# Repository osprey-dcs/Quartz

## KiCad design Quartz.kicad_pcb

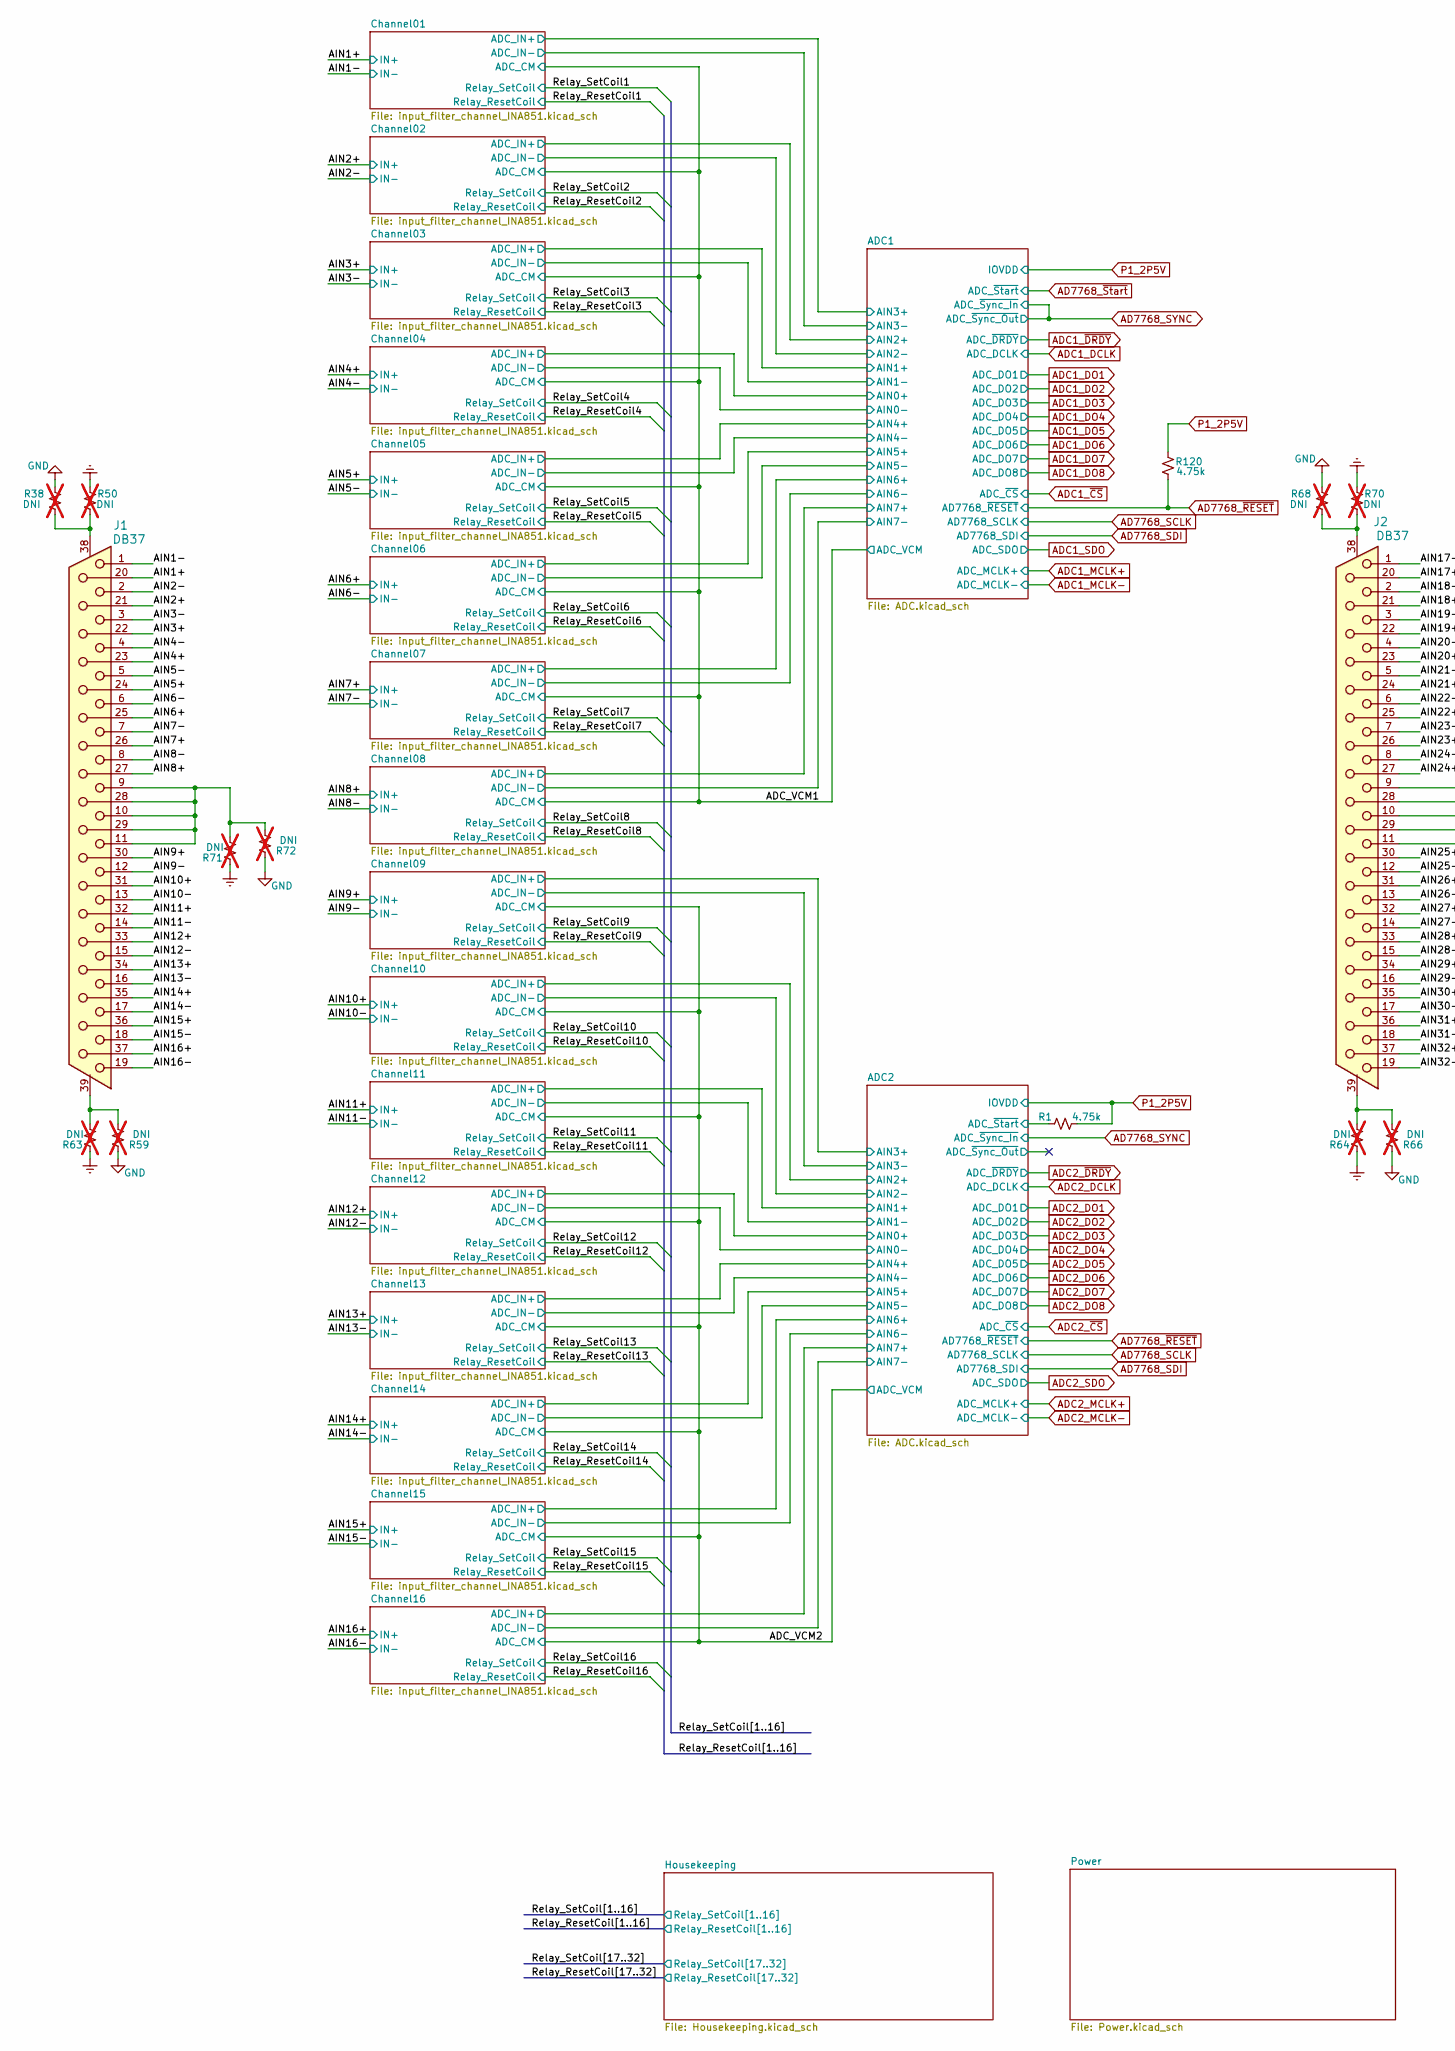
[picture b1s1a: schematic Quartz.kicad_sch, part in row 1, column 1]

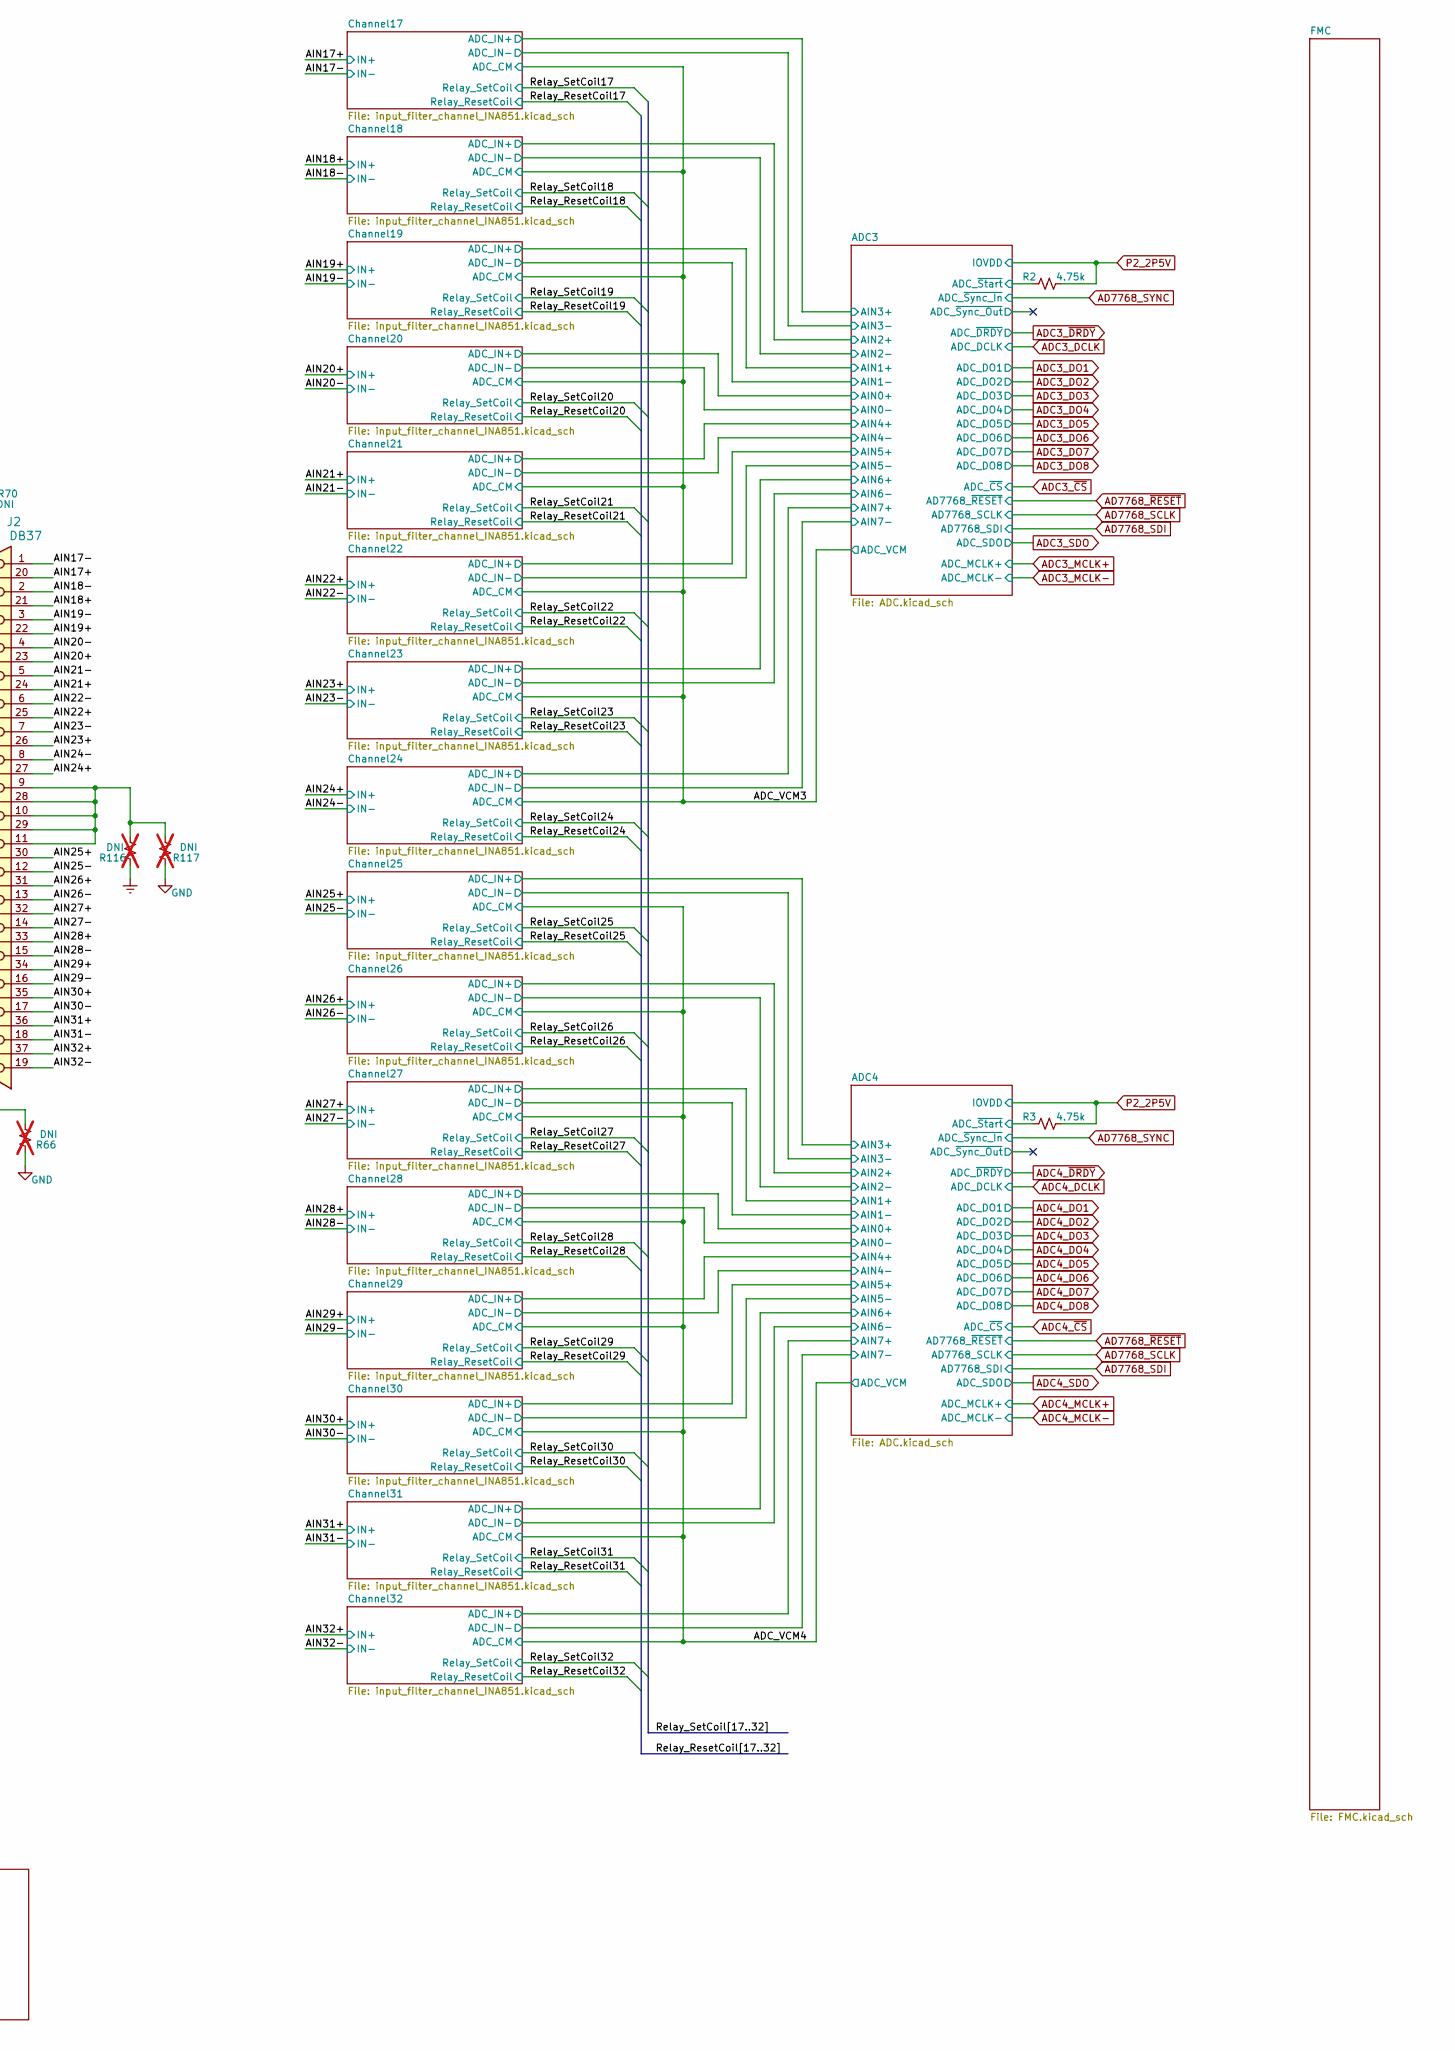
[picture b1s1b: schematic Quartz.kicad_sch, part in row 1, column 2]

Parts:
J1, J2: DB37; CONN_5747847-6_TYC; MPN 5747847-6
R1, R2, R3, R120: 4.75k; R_0402_1005Metric; MPN RC0402FR-074K75L
R38, R50, R59, R63, R64, R66, R68, R70, R71, R72, R116, R117: DNI; R_0805_2012Metric; MPN DNI; not fitted

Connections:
/ADC2/ADC_~Start: R1.1; also elsewhere on the board
/ADC3/ADC_~Start: R2.1; also elsewhere on the board
/ADC4/ADC_~Start: R3.1; also elsewhere on the board
/AIN1+: J1.20; also elsewhere on the board
/AIN1-: J1.1; also elsewhere on the board
/AIN2+: J1.21; also elsewhere on the board
/AIN2-: J1.2; also elsewhere on the board
/AIN3+: J1.22; also elsewhere on the board
/AIN3-: J1.3; also elsewhere on the board
/AIN4+: J1.23; also elsewhere on the board
/AIN4-: J1.4; also elsewhere on the board
/AIN5+: J1.24; also elsewhere on the board
/AIN5-: J1.5; also elsewhere on the board
/AIN6+: J1.25; also elsewhere on the board
/AIN6-: J1.6; also elsewhere on the board
/AIN7+: J1.26; also elsewhere on the board
/AIN7-: J1.7; also elsewhere on the board
/AIN8+: J1.27; also elsewhere on the board
/AIN8-: J1.8; also elsewhere on the board
/AIN9+: J1.30; also elsewhere on the board
/AIN9-: J1.12; also elsewhere on the board
/AIN10+: J1.31; also elsewhere on the board
/AIN10-: J1.13; also elsewhere on the board
/AIN11+: J1.32; also elsewhere on the board
/AIN11-: J1.14; also elsewhere on the board
/AIN12+: J1.33; also elsewhere on the board
/AIN12-: J1.15; also elsewhere on the board
/AIN13+: J1.34; also elsewhere on the board
/AIN13-: J1.16; also elsewhere on the board
/AIN14+: J1.35; also elsewhere on the board
/AIN14-: J1.17; also elsewhere on the board
/AIN15+: J1.36; also elsewhere on the board
/AIN15-: J1.18; also elsewhere on the board
/AIN16+: J1.37; also elsewhere on the board
/AIN16-: J1.19; also elsewhere on the board
/AIN17+: J2.20; also elsewhere on the board
/AIN17-: J2.1; also elsewhere on the board
/AIN18+: J2.21; also elsewhere on the board
/AIN18-: J2.2; also elsewhere on the board
/AIN19+: J2.22; also elsewhere on the board
/AIN19-: J2.3; also elsewhere on the board
/AIN20+: J2.23; also elsewhere on the board
/AIN20-: J2.4; also elsewhere on the board
/AIN21+: J2.24; also elsewhere on the board
/AIN21-: J2.5; also elsewhere on the board
/AIN22+: J2.25; also elsewhere on the board
/AIN22-: J2.6; also elsewhere on the board
/AIN23+: J2.26; also elsewhere on the board
/AIN23-: J2.7; also elsewhere on the board
/AIN24+: J2.27; also elsewhere on the board
/AIN24-: J2.8; also elsewhere on the board
/AIN25+: J2.30; also elsewhere on the board
/AIN25-: J2.12; also elsewhere on the board
/AIN26+: J2.31; also elsewhere on the board
/AIN26-: J2.13; also elsewhere on the board
/AIN27+: J2.32; also elsewhere on the board
/AIN27-: J2.14; also elsewhere on the board
/AIN28+: J2.33; also elsewhere on the board
/AIN28-: J2.15; also elsewhere on the board
/AIN29+: J2.34; also elsewhere on the board
/AIN29-: J2.16; also elsewhere on the board
/AIN30+: J2.35; also elsewhere on the board
/AIN30-: J2.17; also elsewhere on the board
/AIN31+: J2.36; also elsewhere on the board
/AIN31-: J2.18; also elsewhere on the board
/AIN32+: J2.37; also elsewhere on the board
/AIN32-: J2.19; also elsewhere on the board
AD7768_~RESET: R120.1; also elsewhere on the board
Earth: R50.1, R63.1, R64.1, R70.1, R71.1, R116.1; also elsewhere on the board
GND: R38.1, R59.1, R66.1, R68.1, R72.1, R117.1; also elsewhere on the board
unnamed: J1.9, J1.10, J1.11, J1.28, J1.29, R71.2, R72.2
unnamed: J1.38, R38.2, R50.2
unnamed: J1.39, R59.2, R63.2
unnamed: J2.9, J2.10, J2.11, J2.28, J2.29, R116.2, R117.2
unnamed: J2.38, R68.2, R70.2
unnamed: J2.39, R64.2, R66.2
P1_2P5V: R1.2, R120.2; also elsewhere on the board
P2_2P5V: R2.2, R3.2; also elsewhere on the board

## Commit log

2023-12-28 Inital Commit
    Inital Commit
2024-01-02 Updated Schmatics
    Some outdated schematics were in the init commit. Uploded proper revision with tweaks.
2024-01-03 Fixed FMC mapping Issue
    Fixed FMC pin mapping and added FMC pin mapping excel file
2024-01-04 Updated Schematics with recent changes
    Made Updates with recent suggestions.
2024-01-04 Updated Channel 1 and fixes from review
    Updated Channel 1 to use the INA851.
    Fixed the ORNTA part pinout.
    Fixed feedback on LT1763s.
2024-01-08 Schmatic Updates
    Updated:
    ADC MCLK signal
    Removed PMOD connectors
    Added Coax input for iRIG signal with 5V buffer
    Moved around FMC pin mapping
    Changed relay driver chip daisy chain order
2024-01-09 Updated Schematics
    Changes:
    -Moved Input resistors to after Coupling Relay
    -Added diff cap at ADC input
    -Changed the ADC clocking configuration (added quad LVDS driver)
    -Changed some signal names for consistancy
2024-01-11 Updated Schematics with latest suggestions
    updates:
    -Revised Power supply section
    -Changed clock buffer chip for ADC Clock
    - Added additional no pop & jumper parts for board debugging
    -Other small part changes
2024-01-12 Schematic Updates
    Updated:
    -Fixed AMC7823 labels
    -Added present detect signals on FMC
    -Added ferrite beads in Power Section and AFE
    -Added 0R in power section
    -Revised EEPROM connections
2024-01-16 Updated Schematic
    -Changed PPS input signal buffer
    -Made Tweaks to Power Supply section (Many involving the LT3097) as suggested by Trent.
    - general schematic clean up for readability
2024-01-18 Update to Schematics; initial PCB commit
    -Updated Power, Housekeeping, and ADCs sheets.
    -Remapped FMC pins
    -Initial board layout commit
2024-01-22 Updated Layout
    -Additional Layout Work
2024-01-23 Updated Schematics with all suggestions
    -Added pull up resistors on SDO line to FPGA
    -Fixed some I/O flags to properly indicate direction
    -Added Bulk caps on 15V rails
    -Added series caps to AC couple the LVDS clock lines. See AN408 from the manufacture
    -Add Voltage monitor for 1.8V and 5V
2024-01-24 Updated Project
    Schematics:
    -updated level shifting IC's
    -Add notes to level shifters
    -Changed Relay Coil Driver channel mapping
    -Added additional Mounting Hole
    Layout
2024-01-25 Updated Project with Latest Changes
    Project:
    -Added pdf plots of PCB layout
    Schematics:
    -Fixed L8 Pinout
    -Adjusted FMC connections
    -Adjusted level shifter connections
2024-01-26 Push Version before ADC change from 1.8V to 2.5V I/O
2024-01-26 Changed ADCs to run on +2.5V VADJ
    Modified schematic to allow the ADCs to be run from the +2.5V VADJ inputs on the FMC connector.
    -All relevant ERC issues ran been looked into.
    -Still working on all Board DRC issues.
2024-01-29 Completed Schmatic and Layout
    All Schematic and Layout Task are complete with the following exceptions:
    - Adjust Silkscreen Layers
    - Add Osprey Logo and Serial Number
    Note-Removed Files no longer reference in the project
2024-01-29 Updated PCB
    Adjusted Silkscreen
    Added Logo and SN location
2024-01-31 Finalized Design & Board
    Change to design
    -Added resistor options to choose the grounding of input connectors
    -uploaded libraries
    -uploaded generated BOM
    - adjusted mounting holes on front of board by 10mil
    -Changed input AC blocking cap to 10nF from 100nF due to part availability
2024-01-31 Updates to Design
    -Flipped D10 to correct side of board
    -Moved and verified mounting hole position
    - Fixed PNs for R1,R2,R3 and LT8582 part
    -added configurable grounding for DB37 center pins
2024-02-14 Full upload of project as it was for prototype order
    -Fixed issue with L7 footprint as pointed out by sierra circuits
    -Updated all files with up to date info as it was ordered
2024-02-15 add local FP library and fix some model paths
2024-03-11 Updated with all Quartz v1.2 changes
    -Fixed issue with pinouts on current sense chip and Mosfet on 15V split rail section
    -moved DB37 connectors by 30mil for front panel alignment
    - Added 12V test point
2024-03-28 Updated to version 1.2.1
    This update fixes a few production documentation issues.
    The boards will be functionally identical to v1.2.
    With this update and going forward I moved away from version number as a part of filenames
    Updates:
    BOM ITEM 3 GRT155R61C474KE01D -> CGA2B3X7R1H473K050BB (wrong value)
    BOM ITEM 7 GRM1885C1H101JA01D -> GRM1555C1H101JA01D (wrong size)
2024-05-06 Use more approriate build time.
2024-05-06 Fix typo in manufacturing date change.
2024-09-09 Saved project as a Kicad8.0 Project
    Saved project as a Kicad8.0 Project
2025-02-25 fix FMC schematic name
2025-02-25 add OSH 1.2 license
2025-02-26 Updating design to cover reworks
    Updating design to cover reworks.
    This should now match what has been delivered to NASA GRE-ATF after the board reworks.
    All outputs have been regenerated
    Changes are:
    1)Changed the clock splitter part to a 2.5V compatible part
    2)Changed some caps on the MCLK lines to 0R resitors
2025-03-05 Added TestPoints Descriptions in Documentation
    Added .pdf of TestPoints Descriptions in Documentation
2025-04-08 Opened & Saved Project in Kicad 9
    - Opened & Saved Project in Kicad 9
    - Added .gitignore from main
    - Added sym-lib-table to link the unchanged symbol libs to the project
2025-04-08 Updated and Condensed Project Symbol Libraries
    - Added Symbols for part used in main(Quartz v2 branch)
    -ADM1185
    -TPS275
    -TPS561208
    - Removed outdated/unused Symbol libraries
    - max4896 (project already copied contents to AD7768_Digitizer_SLib)
2025-04-09 Fixed Serveral ERC errors
    Fixed Several ERC errors
    - Ignored off-grid connections errors
    - Updated a number of symbols from the Kicad default library. This should have no visual change
    - Power:Ground
    - Power:Earth
    - Device:LED
2025-04-09 Fixed remaining ERC errors and Warnings
    No changes affecting copper were made.
    At the end of this commits changes all changes from this and the previous two commits were pulled into the PCB.
    No changes to the layout occurred and no additional pcb error or warning were made
    Detailed Changes:
    -Saved the Local Symbol to the project symbol lib and relinked for
    - Q1 & Q2 (looks like symbol was removed from std lib)
2025-04-11 Verified 'Must do changes' implemented all 'should do' changes
    Must do Changes that have been verified:
    -Change the Clock divider chip to the 2,5V part
    -Remove AC coupling caps in clock lines
    Should do changes implmented
    - Add pull up resistor to ADC reset lines
    - Internal termination of PPS (when unused)
2025-04-17 Improved grounding of Relay ICs
    -Added GND Via for Relay IC's and removed conflicting 3.3V rail
    - This has been replaced with a zone
    - Adjusted Zone around one of the inductors to avoid a copper sliver
2025-04-17 Added Calibration EEPROM
    -Added Calibration EEPROM
    -Changed WP headers to 100mil spaced part
2025-04-17 Fixed Grounding under Clk divider
    Added Ground Vias Under the Si5330 Chip
2025-04-17 Changed Cal EEPROM to run off 2.5V
    Changed Cal EEPROM to run off 2.5V
2025-04-18 Create output job, a couple of fixes
    - Created a output job file.
    - This will generate all the output products in a consistant way
    - This was tested OK agianst maunally creating the output objects
    - Removed Output Objects for version control
    - Removed a Power ERC net object from the CAL EEPROM to fix an ERC error
    - Added Explict Manufacturer for the test points for ordering clarity
2025-04-18 Moved EEPROM WP connectors to correct side
    -Moved EEPROM WP connectors to correct side
2025-04-18 Small Layout Tweaks before ordering
    -Added Gnd Via on P2 pads C36 & D37
    -Moved ground Vias to under pad on U35 (like Version2)
    -Cleaned up traces around U33 and removed faulty pour
    -Add ground vias under U13
    -Verified Q3 pin 1 marker is in the correct location (pin '3' as built in the layout is pin one of the package)
2025-04-18 Update Quartz-OutputJob for proper csv delimiting
    - fixed BOM export to use standard csv delimiting
